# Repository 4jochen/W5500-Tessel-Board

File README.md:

W5500-Ethernet-Board
==================

Ethernet Board with WIZnet W5500 Hardwired TCP/IP + MAC + PHY chip
for:
Tessel - http://www.technical.io/
Espruino - http://www.espruino.com/
mikroBUS - http://www.mikroe.com/mikrobus/

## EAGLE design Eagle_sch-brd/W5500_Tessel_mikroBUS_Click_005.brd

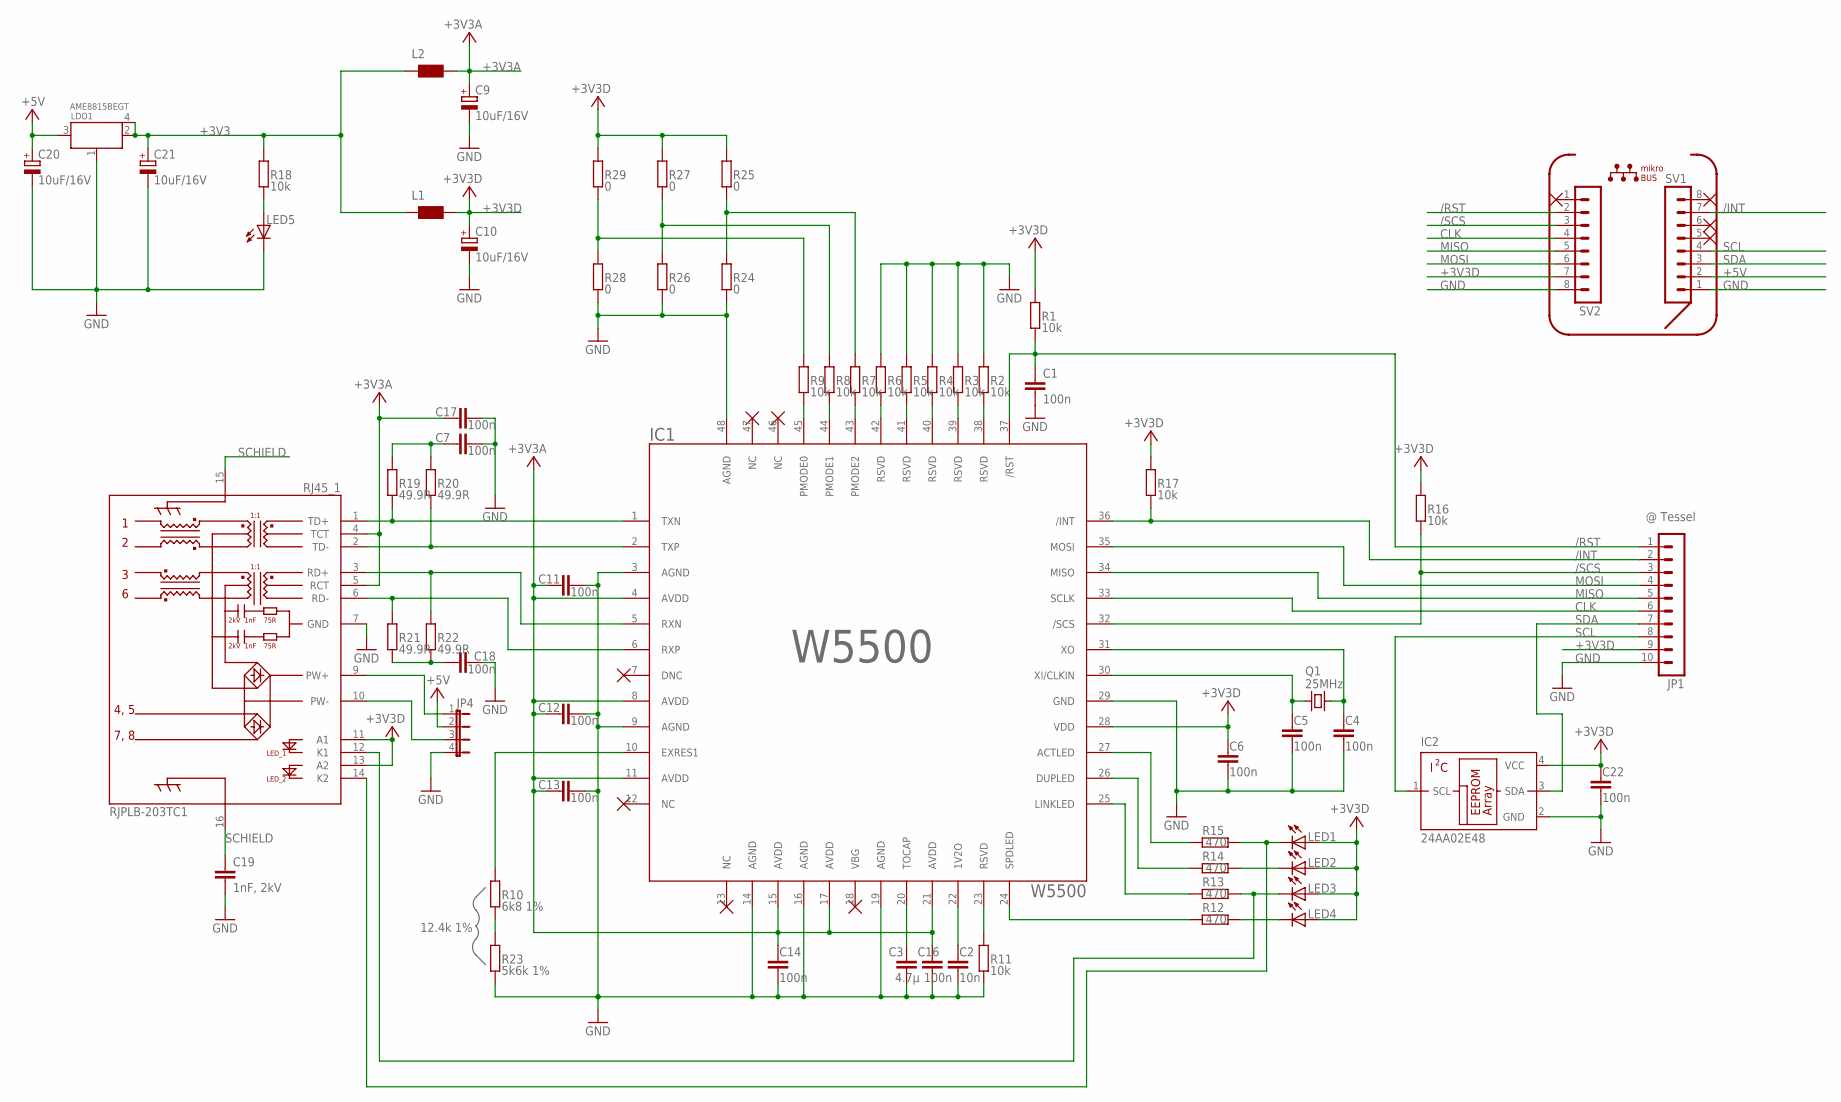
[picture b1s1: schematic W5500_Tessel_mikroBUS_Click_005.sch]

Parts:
C1: 100n; C0603K
C2: 10n; C0402K
C3: 4.7µ; C0603K
C4, C5, C6, C7, C11, C12, C13, C14, C16, C17, C18, C22: 100n; C0402K
C9, C10, C20, C21: 10uF/16V; A/3216-18R
C19: 1nF, 2kV; C3216
IC1: W5500; LQFP48
IC2: 24AA02E48; SOT23-5L
JP1: @ Tessel; MA10-1
JP4: JP4E; JP4
L1, L2: WE-CBF_0603; 0603
LDO1: AME8815BEGT; SOT223
LED1, LED2, LED3, LED4, LED5: LEDCHIPLED_0603; CHIPLED_0603
Q1: 25MHz; SMD02502-4
R1, R2, R3, R4, R5, R6, R7, R8, R9, R11, R16, R17, R18: 10k; R0402
R10: 6k8 1%; R0402
R12, R13, R14, R15: 470; R0402
R19, R20, R21, R22: 49.9R; R0402
R23: 5k6k 1%; R0402
R24, R25, R26, R27, R28, R29: 0; R0402
RJ45_1: RJPLB-203TC1; RJPLB-203
SV1, SV2: MA08-1

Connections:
+3V3: C21.+, L1.2, L2.2, LDO1.2, LDO1.4, R18.2
+3V3A: C9.+, C11.1, C12.1, C13.1, C14.1, C16.1, C17.1, IC1.4 (AVDD), IC1.8 (AVDD), IC1.11 (AVDD), IC1.15 (AVDD), IC1.17 (AVDD), IC1.21 (AVDD), L2.1, RJ45_1.4 (TCT), RJ45_1.5 (RCT)
+3V3D: C6.1, C10.+, C22.1, IC1.28 (VDD), IC2.4 (VCC), JP1.9, L1.1, LED1.A, LED2.A, LED3.A, LED4.A, R1.2, R16.2, R17.2, R25.2, R27.2, R29.2, RJ45_1.11 (A1), RJ45_1.13 (A2), SV2.7
+5V: C20.+, JP4.2, LDO1.3, SV1.2
/INT: IC1.36 (/INT), JP1.2, R17.1, SV1.7
/RST: C1.1, IC1.37 (/RST), JP1.1, R1.1, SV2.2
/SCS: IC1.32 (/SCS), JP1.3, R16.1, SV2.3
ACTLED: IC1.27 (ACTLED), R15.1
CLK: IC1.33 (SCLK), JP1.6, SV2.4
GND: C1.2, C2.2, C3.2, C4.2, C5.2, C6.2, C7.2, C9.-, C10.-, C11.2, C12.2, C13.2, C14.2, C16.2, C17.2, C18.2, C19.2, C20.-, C21.-, C22.2, IC1.3 (AGND), IC1.9 (AGND), IC1.14 (AGND), IC1.16 (AGND), IC1.19 (AGND), IC1.29 (GND), IC1.48 (AGND), IC2.2 (GND), JP1.10, JP4.4, LDO1.1, LED5.C, R2.2, R3.2, R4.2, R5.2, R6.2, R11.1, R23.1, R24.1, R26.1, R28.1, RJ45_1.7 (GND), SV1.1, SV2.8
MISO: IC1.34 (MISO), JP1.5, SV2.5
MOSI: IC1.35 (MOSI), JP1.4, SV2.6
unnamed: IC1.25 (LINKLED), R13.1
unnamed: R10.1, R23.2
unnamed: IC1.23 (RSVD), R11.2
unnamed: IC1.38 (RSVD), R2.1
unnamed: IC1.39 (RSVD), R3.1
unnamed: IC1.40 (RSVD), R4.1
unnamed: IC1.41 (RSVD), R5.1
unnamed: IC1.42 (RSVD), R6.1
unnamed: IC1.43 (PMODE2), R7.1
unnamed: IC1.44 (PMODE1), R8.1
unnamed: IC1.45 (PMODE0), R9.1
unnamed: R9.2, R28.2, R29.1
unnamed: R8.2, R26.2, R27.1
unnamed: R7.2, R24.2, R25.1
unnamed: IC1.10 (EXRES1), R10.2
unnamed: C2.1, IC1.22 (1V2O)
unnamed: C3.1, IC1.20 (TOCAP)
unnamed: IC1.24 (SPDLED), R12.1
unnamed: IC1.26 (DUPLED), R14.1
unnamed: LED4.C, R12.2
unnamed: LED3.C, R13.2, RJ45_1.12 (K1)
unnamed: LED2.C, R14.2
unnamed: LED1.C, R15.2, RJ45_1.14 (K2)
unnamed: C4.1, IC1.31 (XO), Q1.3 (2)
unnamed: C5.1, IC1.30 (XI/CLKIN), Q1.1
unnamed: LED5.A, R18.1
unnamed: C7.1, R19.2, R20.2
unnamed: C18.1, R21.1, R22.1
POE+: JP4.1, RJ45_1.9 (PW+)
POE-: JP4.3, RJ45_1.10 (PW-)
RXN: IC1.6 (RXP), R21.2, RJ45_1.6 (RD-)
RXP: IC1.5 (RXN), R22.2, RJ45_1.3 (RD+)
SCHIELD: C19.1, RJ45_1.15 (SCHIELD_1), RJ45_1.16 (SCHIELD_2)
SCL: IC2.1 (SCL), JP1.8, SV1.4
SDA: IC2.3 (SDA), JP1.7, SV1.3
TXN: IC1.2 (TXP), R20.1, RJ45_1.2 (TD-)
TXP: IC1.1 (TXN), R19.1, RJ45_1.1 (TD+)

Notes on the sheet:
W5500
12.4k 1%
mikro BUS

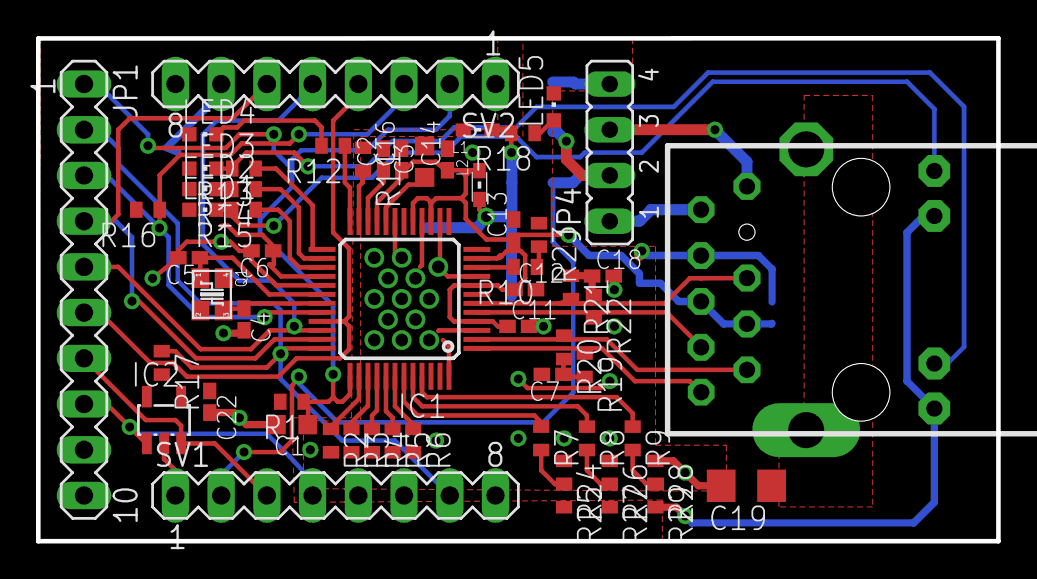
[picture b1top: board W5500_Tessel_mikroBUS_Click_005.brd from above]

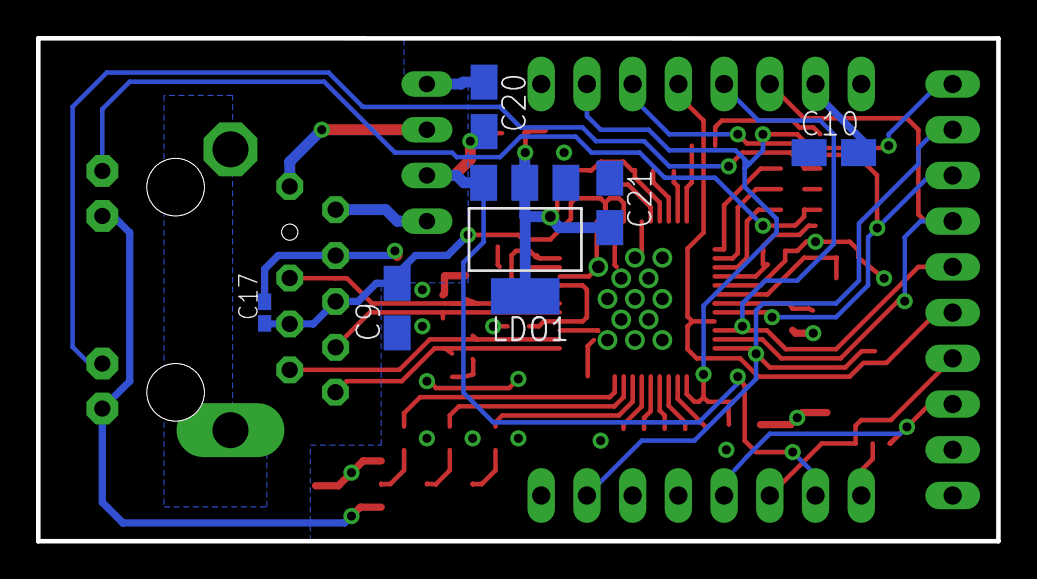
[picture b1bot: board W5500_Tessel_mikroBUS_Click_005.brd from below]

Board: 2 copper layers, 53.3 x 27.9 mm, 65 parts (6 on the bottom side), 49 nets.

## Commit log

2013-09-03 uploaded lbr, sch and brd files
2013-09-12 added mikroBUS footprint for Espruino and MikroE
2013-09-23 beta version 005 - ready for prototype
    made it Tessel, Espruion and MikroElektronika "Click" compatible
    need to add the (TM) Logos
    created PDF for use without Eagle also
2013-09-23 changed page 3

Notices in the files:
parts and their libraries:
wuerth-elektronik: Copyright: Würth Elektronik eiSos
